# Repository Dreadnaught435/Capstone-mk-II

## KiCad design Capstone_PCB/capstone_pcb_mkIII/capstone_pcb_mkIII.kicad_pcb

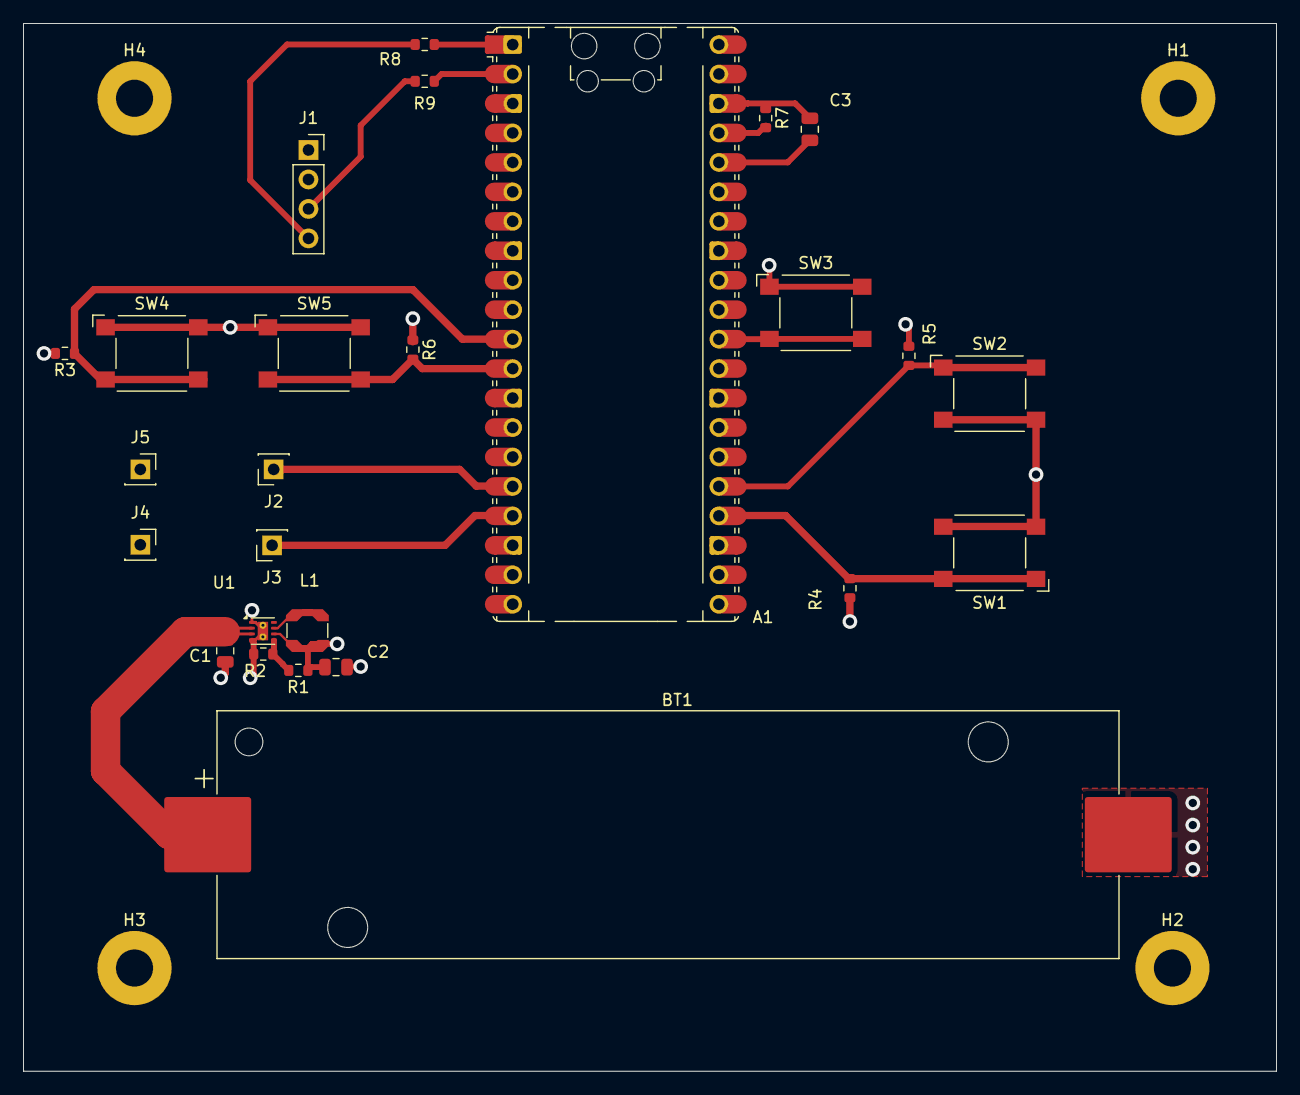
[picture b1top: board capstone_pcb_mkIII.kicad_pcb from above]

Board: 4 copper layers, 108.0 x 90.4 mm, 30 parts (0 on the bottom side), 17 nets.

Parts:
A1: RaspberryPi_Pico; RaspberryPi_Pico_Common_Unspecified
BT1: Battery_Cell; BatteryHolder_Keystone_1042_1x18650
C1, C2, C3: 10uF; C_0805_2012Metric
H1, H2, H3, H4: MountingHole_Pad; MountingHole_3.2mm_M3_Pad
J1: DISPLAY_HEADER; PinSocket_1x04_P2.54mm_Vertical
J2: UART_TX; PinSocket_1x01_P2.54mm_Vertical
J3: UART_RX; PinSocket_1x01_P2.54mm_Vertical
J4: GND; PinSocket_1x01_P2.54mm_Vertical
J5: 3V3; PinSocket_1x01_P2.54mm_Vertical
L1: 2.2uH; L_Coilcraft_LPS3314
R1: 1.8MΩ; R_0603_1608Metric
R2: 576kΩ; R_0603_1608Metric
R3, R4, R5, R6: 100kΩ; R_0603_1608Metric
R7: 0; R_0603_1608Metric
R8, R9: 10k; R_0603_1608Metric
SW1, SW2, SW3, SW4, SW5: SW_Push; SW_SPST_Omron_B3FS-100xP
U1: TPS62125DSG; WSON-8-1EP_2x2mm_P0.5mm_EP0.9x1.6mm_ThermalVias

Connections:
GND: A1.3 (GND), A1.8 (GND), A1.13 (GND), A1.18 (GND), A1.23 (GND), A1.28 (GND), A1.38 (GND), BT1.2 (-), C1.2, C2.2, C3.2, H1.1, H2.1, H3.1, H4.1, J1.2, J4.1, R2.2, R7.1, SW1.2, SW2.2, SW3.1, SW4.1, SW5.1, U1.1 (PGND), U1.4 (AGND), U1.9 (PAD)
unnamed: A1.37 (3V3_EN), R7.2
unnamed: A1.1 (GPIO0), R8.2
unnamed: A1.2 (GPIO1), R9.2
unnamed: A1.11 (GPIO8), R3.1, SW4.2
unnamed: A1.12 (GPIO9), R6.2, SW5.2
unnamed: A1.16 (GPIO12), J2.1
unnamed: A1.17 (GPIO13), J3.1
unnamed: A1.24 (GPIO18), R4.1, SW1.1
unnamed: A1.25 (GPIO19), R5.2, SW2.1
unnamed: A1.30 (RUN), SW3.2
unnamed: BT1.1 (+), C1.1, U1.2 (VIN), U1.3 (EN)
unnamed: J1.3, R9.1
unnamed: J1.4, R8.1
unnamed: R1.2, R2.1, U1.5 (FB)
unnamed: L1.1, U1.7 (SW)
V_BC: A1.36 (3V3), C2.1, C3.1, J1.1, J5.1, L1.2, R1.1, R3.2, R4.2, R5.1, R6.1, U1.6 (VOS)

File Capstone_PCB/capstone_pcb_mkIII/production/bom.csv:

Designator,Footprint,Quantity,Value,LCSC Part #
A1,RaspberryPi_Pico_Common_Unspecified,1,RaspberryPi_Pico,
BT1,BatteryHolder_Keystone_1042_1x18650,1,Battery_Cell,
"C1, C2, C3",0805,3,10uF,
J1,PinSocket_1x04_P2.54mm_Vertical,1,DISPLAY_HEADER,
J2,PinSocket_1x01_P2.54mm_Vertical,1,UART_TX,
J3,PinSocket_1x01_P2.54mm_Vertical,1,UART_RX,
J4,PinSocket_1x01_P2.54mm_Vertical,1,GND,
J5,PinSocket_1x01_P2.54mm_Vertical,1,3V3,
L1,L_Coilcraft_LPS3314,1,2.2uH,
R1,0603,1,1.8MΩ,
R2,0603,1,576kΩ,
"R3, R4, R5, R6",0603,4,100kΩ,
R7,0603,1,0,
"R8, R9",0603,2,10k,
"SW1, SW2, SW3, SW4, SW5",SW_SPST_Omron_B3FS-100xP,5,SW_Push,
U1,WSON-8-1EP_2x2mm_P0.5mm_EP0.9x1.6mm_ThermalVias,1,TPS62125DSG,

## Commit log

2026-02-24 initial commit for new project
2026-02-26 updated pcb to have better traces, moved transmit/receive closer to processor, made their traces the same length
2026-03-05 updated schematics to have component values
2026-03-12 new pcb designed in kicad with pi pico
2026-03-13 pcb almost done, few more errors to iron out tomorrow
2026-03-31 new pcb
2026-03-31 safety commit, im about to mess with capstone_code to try to get it to work with the vscode pico environment, this is here to revert to if i break something
2026-04-02 new project, updated cmakelists, capstone_display, and capstone_main
2026-04-02 can talk to display, but not configured correctly
2026-04-03 display now works, using built in pico library. will rewrite for complexity if time permits
2026-04-03 added first implementation of interrupt, interrupt does trigger
2026-04-03 both interrupts work
2026-04-03 added debouncing
2026-04-04 added morse file, timestamp vars, interrupt calls interpret_buttons properly
2026-04-04 interrupts now gather timestamps of presses, for interpret_buttons to handle
2026-04-04 added morse decoding logic
2026-04-05 timestamps from interrupts work correctly
2026-04-05 added . and - to font
2026-04-06 morse decoder works
2026-04-06 everything is done except for uart, software and hardware
2026-04-07 uart done, doesnt work, possible memory leak
2026-04-08 IT FUCKING W0RKS. display still hangs occasionally, maybe look into that?
2026-04-09 works well. no space, occasionally transmits with an empty space at the beginning of rec. put reset statement earlier in interrupt handler?
